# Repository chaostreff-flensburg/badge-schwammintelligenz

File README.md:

# badge-schwammintelligenz

## Ideensammlung
- PCB mit Gehirn-Form und Schwamm-Farbe
  - gelber Lötstopplack
  - nacktes FR4 als Kontrastfarbe für Porösität des Schwammes
  - Konturlinien in schwarzem oder weißem Bestückungsdruck
- viele sehr kleine LEDs auf der Vorderseite
  - blitzen auf, um Neuronen zu mimen
  - mit [Charlieplexing](https://en.wikipedia.org/wiki/Charlieplexing#Origin) kann man 110 LEDs mit nur 11 Pins einzeln ansteuern
    - (`nLedsMax = nGpio * (nGpio - 1)`)
    - [Beispielcode für Charlieplexing](https://goodarduinocode.com/guides/charlieplexing) -> Zeilenweise ansteuern
  - [XINGLIGHT XL0201UWC](https://jlcpcb.com/partdetail/XINGLIGHT-XL0201UWC/C965789) wäre z.B. nur 0,7 mm * 0,4 mm groß (Pads komplett unter dem Package) und kostet nur 0,0326 USD / St. bei 5000 St. Abnahme
- Kompatibilität zu Mesh-Cat-Ears?
  - [Rudelblinken](https://github.com/zebreus/rudelblinken)
  - Die laufen mit BLE auf einem ESP32-C3
  - Wir könnten denselben Controller nutzen, um mit den Katzenohren meshen zu können
- ein Taster auf der Rückseite, um einen Puls auszulösen
  - erstmal an den eigenen LEDs
  - langfristig sonst auch auf Gehirnen in der Nähe
  - evtl. jeder Mesh-Teilnehmer eine eigene LED?
  - 3-4 Taster (Soft touch) (Typ [Alps SKPM](https://tech.alpsalpine.com/e/products/detail/SKPMANE010/)?)

## Implementierung der Farben

Die Platine wird mit **gelbem Lötstopplack** und **weißem Bestückungsdruck** gefertigt.

Kupfer auf der Rückseite minimal halten und wo möglich unter dem Kupfer der Oberseite verlegen.

Der Entwurf sieht folgendermaßen aus:

### Farbaufbau

| Farbe | Objekte | Beteiligte Lagen | Notizen |
| --- | --- | --- | --- |
| weiß | ??? | F.Silkscreen | Bestückungsdruck (muss auf Lötstopplack liegen) |
| silber | ??? | F.Cu, F.Mask | freies Kupfer mit HASL Finish |
| hellergelb | Schwammoberfläche | F.Mask | blankes FR4 (kein Kupfer auf der Rückseite) - ca. `e9d645ff` |
| hellgelb | Vertiefung flach | none | Lötstopplack auf FR4 (kein Kupfer auf der Rückseite) - ca. `f6c50eff` |
| dunkelgelb | Vertiefung tief | F.Cu | Lötstopplack auf Kupfer - ca. `e8b203ff` |
| grüngelb | --- | F.Cu, F.Mask | blankes FR4 mit Kupfer auf der Rückseite |

### Lagenaufbau

| Lage | Objekte |
| --- | --- |
| F.Cu | union( silber, dunkelgelb ) |
| F.Mask | invert( union( weiß, hellgelb, dunkelgelb ) ) |
| F.Silkscreen | weiß |

## BOM

Die folgenden Preise beziehen sich auf ein einzelnes Badge wenn wir Material für 50 Stück kaufen.

- JLCPCB Preis vom 2026-06-15
  - PCB ca. 100 mm x 100 mm
  - Silkscreen gleb
  - 1,6 mm dick
  - LeadFree HASL
  - je 110 St. XINGLIGHT XL-0201UWC (LCSC C965789) von JLCPCB auf der Vorderseite bestückt
  - 258,80 € (Material und Produktion) + 48,03 € (Versand EuroPacket) = 306,83 €
  - Es ist mit 2 Wochen Lieferzeit zu rechnen, wenn es keine Rücksprachen braucht

| Anzahl | Preis | Bezeichnung |
| --- | --- | --- |
| 1 | 6,14 € | PCB mit LEDs (Stand 2026-06-15 von JLCPCB teilbestückt) |
| 1 | ca. 4 € | ESP32-C3 |
| ? | ??? | ??? |

## Firmware

Liegt in `firmware/` und läuft auf dem Waveshare ESP32-C3-Zero.

**Für alle, die einfach ein Badge haben:** Auf https://schwammhirn.c3fl.de/ gibt es alles in
einer Seite. Badge per USB anstecken, „Firmware flashen“ klicken, Port wählen. Danach per
Bluetooth verbinden und steuern. Keine Installation nötig, Chrome oder Edge am Desktop reicht
(zum Steuern auch Chrome auf Android, auf dem iPhone der Browser „Bluefy“).

**Zum Mitentwickeln:** Bauen wahlweise mit der Arduino IDE (Board „Waveshare ESP32-C3-Zero“,
Bibliothek NimBLE-Arduino 2.x) oder mit PlatformIO im Repo-Root: `pio run -t upload`.

- `firmware/led_map.h` wird von `tools/gen_led_map.py` aus `pcb/pcb.kicad_pcb` erzeugt
  (Pin-Paar, Position und Hirnareal jeder LED, die Areale aus den Beschriftungen auf
  Cmts.User). Nach Layoutänderungen neu ausführen, das Skript schreibt auch `web/led_map.js`.
- Ein Timer-Interrupt scannt die Charlieplex-Matrix mit 4 Bit Helligkeit, `loop()`
  rendert Animationen in einen Framebuffer.
- Taster: kurz drücken löst eine Welle aus (auch auf Badges in Reichweite), lang drücken
  wechselt den Modus (Neuronen, Wellen, Cortex, Suche, Laufschrift, Löt-Test). Im Löt-Test startet kurz
  drücken den Durchlauf von vorne. Alle drei Taster liegen auf demselben Eingang.
- Sync: Badges senden Modus, Tempo, Helligkeit, Schriftlayout und Phase per BLE-Advertising.
  Die höchste Änderungsgeneration gewinnt, bei Gleichstand die kleinere ID. Kein
  Verbindungsaufbau nötig. Der Text selbst wird nicht übertragen.
- BLE-Anzeigename ist standardmäßig `Schwammhirn-<ID>` aus der Bluetooth-MAC, änderbar.
  Die Web-Seite findet Badges über die Herstellerkennung im Werbepaket, unabhängig vom Namen.

### Modi

| Modus | Kommando | Was passiert |
| --- | --- | --- |
| Neuronen | `mode neurons` | zufällige Blitze, die ausklingen (Standard) |
| Wellen | `mode pulse` | Ringe laufen von einem zufälligen Punkt nach außen |
| Suche | `mode radar` | Radarstrahl kreist um die Mitte. Je Badge in Reichweite ein Herzschlag-Ring von innen nach außen, schneller und heller je näher (Signalstärke der Werbepakete, −95 dBm weit bis −65 dBm direkt daneben) |
| Cortex | `mode cortex` | ein Hirnareal (Frontal-, Parietal-, Temporal-, Okzipitallappen, Kleinhirn, Stammhirn, aus den Beschriftungen im PCB) blitzt auf, schwächere Wellen laufen von dort in den Rest |
| Laufschrift | `mode text` | Text läuft durch, Größe und Abstand oben einstellbar |
| Löt-Test | `mode test` | füllt jede Zeile LED für LED, dann dunkel, nächste Zeile; danach dasselbe spaltenweise. Jede neue LED wird gemeldet. Fehlt eine LED, ist es die Lötstelle; fehlt eine Zeile oder Spalte, der GPIO oder sein 10-Ω-Widerstand. Wird nicht synchronisiert und nicht gespeichert. |
| Malen | `mode remote` | zeigt ein Rohbild, das per `frame` gesendet wurde (Web-Seite: LEDs antippen) |

### Kommandos (Serial und BLE)

Dieselben Textkommandos gehen über Serial (115200 Baud, USB) und über BLE. BLE nutzt den
Nordic-UART-Service (Schreiben auf `6E400002-…`, Antworten als Notify auf `6E400003-…`),
jede BLE-Terminal-App funktioniert also, zum Beispiel „Serial Bluetooth Terminal“ auf Android.
Eine Zeile pro Kommando, Antwort beginnt mit `ok` oder `err`.

| Kommando | Bedeutung |
| --- | --- |
| `mode <name>` oder `mode <0-6>` | Modus wählen: `neurons`, `pulse`, `cortex`, `radar`, `text`, `test`, `remote` |
| `text <Text>` | Laufschrift setzen, max. 63 Zeichen, Umlaute werden ersetzt, schaltet auf Laufschrift |
| `tsize <1-5>` | Schriftgröße (Leinwand-Pixel pro Font-Pixel), Standard 3 |
| `ty <0-30>` | Abstand der Schrift vom oberen Rand, Standard 6 |
| `speed <0-100>` | Tempo aller Animationen, Standard 4 |
| `bright <1-15>` | Helligkeit, Standard 15 |
| `pulse` oder `pulse <LED 0-109>` | Welle auslösen, auch auf Badges in Reichweite. Im Löt-Test: Durchlauf neu starten |
| `frame <220 Hex-Zeichen>` | Rohbild, ein Byte Helligkeit pro LED in D-Reihenfolge, schaltet auf Malen |
| `name <Name>` | BLE-Anzeigename, max. 20 Zeichen, leer = Standard `Schwammhirn-<ID>` |
| `sync on` / `sync off` | Einstellungen von Badges in der Nähe übernehmen oder ignorieren |
| `mirror on` / `mirror off` | Framebuffer etwa 10-mal pro Sekunde als `F<220 Hex>` per BLE-Notify streamen (Live-Bild der Web-Seite) |
| `peers` | Badges in Reichweite mit ID, Signalstärke, Nähe und Alter des letzten Pakets auflisten |
| `status` | Zustand ausgeben: Modus, Tempo, Helligkeit, Schriftlayout, Text, Sync, Generation, ID, Badges in Reichweite, Name |

Modus, Tempo, Helligkeit, Text, Schriftlayout und Name bleiben über Neustarts erhalten.

### Web-Steuerung

Unter https://schwammhirn.c3fl.de/ oder lokal aus `web/index.html`. „Mit Badge verbinden“
drücken, dann Modi, Text, Regler und Umbenennen. Zeigt live das Bild des Badges, im Modus
„Malen“ lassen sich LEDs antippen. Ohne Verbindung läuft dieselbe Animation als Simulation
1:1 auf der Platinenkontur, so lässt sich zum Beispiel Laufschrift vorab beurteilen.
Web Bluetooth braucht HTTPS oder localhost, deshalb funktioniert Verbinden aus dem
Dateisystem nur in Chrome, das `file://` als sicher behandelt.

Firmware flashen ohne Toolchain: Button „Firmware flashen“ (ESP Web Tools, Chrome/Edge am
Desktop). Die Binaries liegen in `web/flash/`, die Seite zeigt den Commit-Hash der Version.
Nach einer Firmware-Änderung: `pio run`, Code committen, dann `tools/export_firmware.sh` und
die Binaries als eigenen Commit nachschieben.

Deployment: Das `Dockerfile` im Repo-Root liefert `web/` per nginx aus. In Coolify eine
Ressource vom Typ „Public Repository“ mit Build Pack „Dockerfile“ anlegen, Port 80, Domain
eintragen. HTTPS macht Coolify per Let's Encrypt. Nach jedem Merge einmal redeployen.

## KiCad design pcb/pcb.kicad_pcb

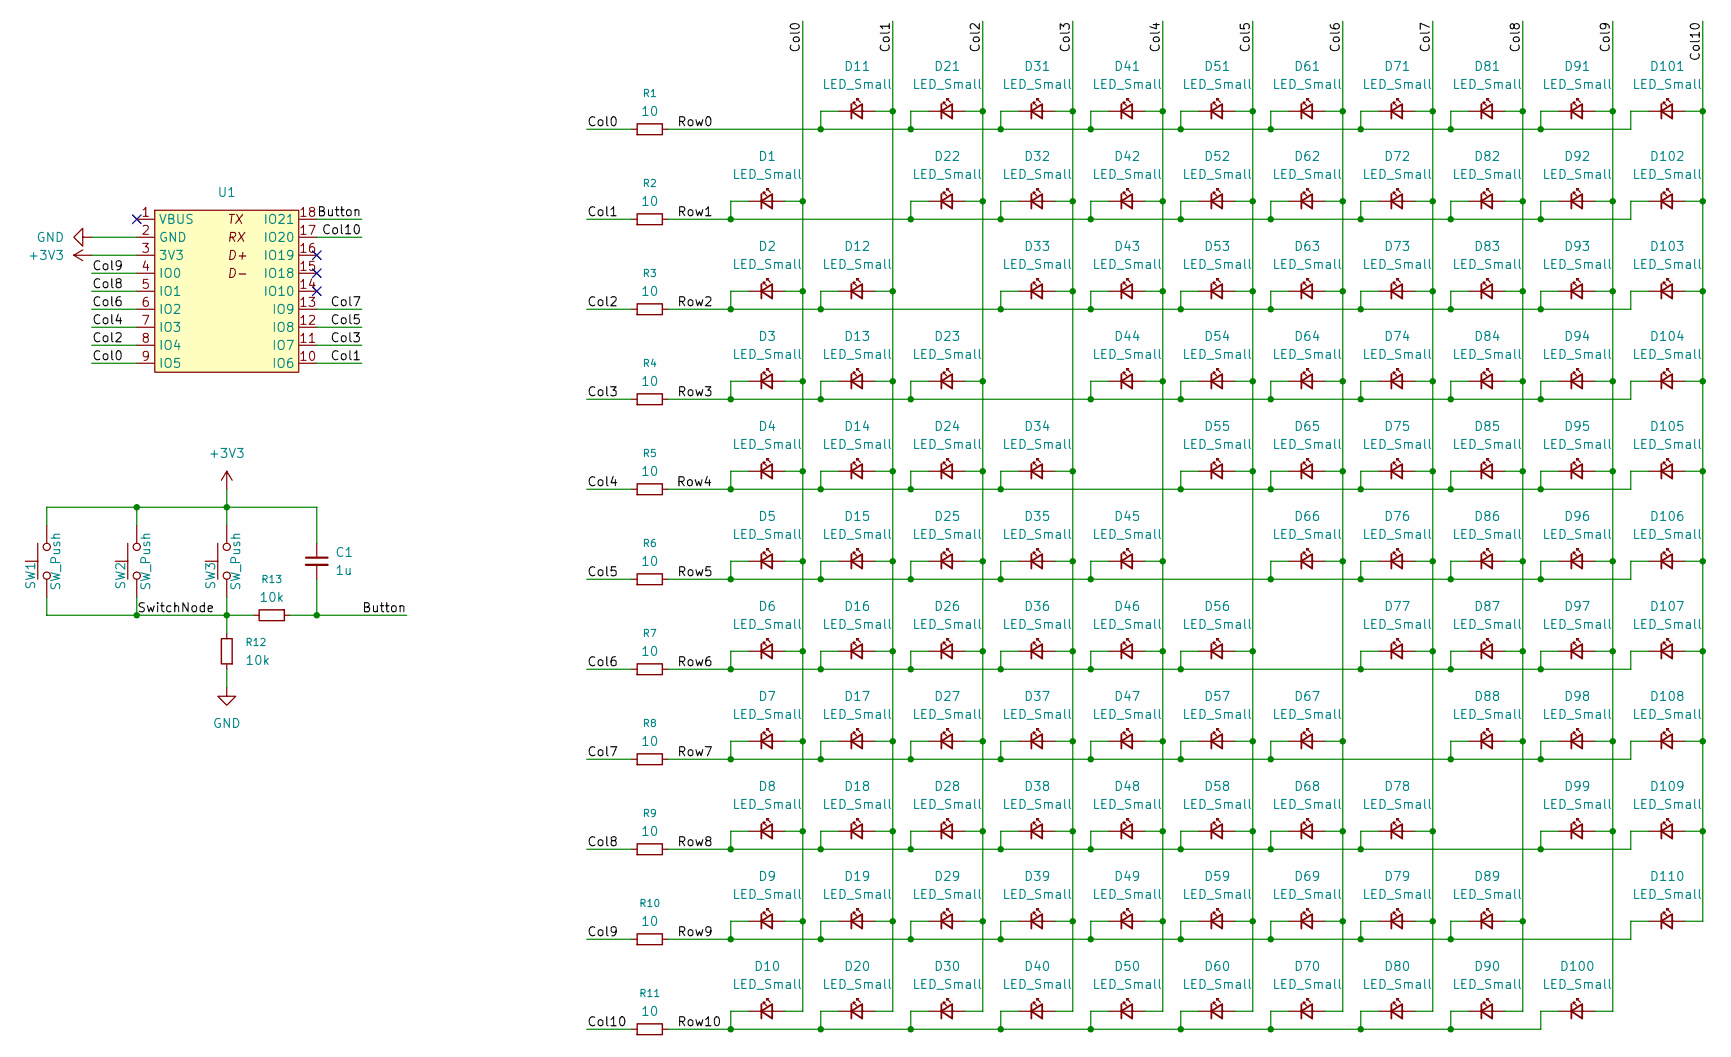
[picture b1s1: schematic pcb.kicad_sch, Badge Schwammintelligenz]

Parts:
C1: 1u; C_0805_2012Metric_Pad1.18x1.45mm_HandSolder
D1, D2, D3, D4, D5, D6, D7, D8, D9, D10, D11, D12, D13, D14, D15, D16, D17, D18, D19, D20, D21, D22, D23, D24, D25, D26, D27, D28, D29, D30, D31, D32, D33, D34, D35, D36, D37, D38, D39, D40, D41, D42, D43, D44, D45, D46, D47, D48, D49, D50, D51, D52, D53, D54, D55, D56, D57, D58, D59, D60, D61, D62, D63, D64, D65, D66, D67, D68, D69, D70, D71, D72, D73, D74, D75, D76, D77, D78, D79, D80, D81, D82, D83, D84, D85, D86, D87, D88, D89, D90, D91, D92, D93, D94, D95, D96, D97, D98, D99, D100, D101, D102, D103, D104, D105, D106, D107, D108, D109, D110: LED_Small; XL-0201; LCSC C965789
R1, R2, R3, R4, R5, R6, R7, R8, R9, R10, R11: 10; R_0805_2012Metric_Pad1.20x1.40mm_HandSolder
R12, R13: 10k; R_0805_2012Metric_Pad1.20x1.40mm_HandSolder
SW1, SW2, SW3: SW_Push; SW_Push_1P1T_NO_Alps_SPEH
U1: Waveshare-ESP32-Cx-Zero

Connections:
+3V3: C1.1, SW1.2, SW2.2, SW3.2, U1.3 (3V3)
/Button: C1.2, R13.1, U1.18 (IO21)
/Col0: D1.2 (A), D2.2 (A), D3.2 (A), D4.2 (A), D5.2 (A), D6.2 (A), D7.2 (A), D8.2 (A), D9.2 (A), D10.2 (A), R1.1, U1.9 (IO5)
/Col1: D11.2 (A), D12.2 (A), D13.2 (A), D14.2 (A), D15.2 (A), D16.2 (A), D17.2 (A), D18.2 (A), D19.2 (A), D20.2 (A), R2.1, U1.10 (IO6)
/Col2: D21.2 (A), D22.2 (A), D23.2 (A), D24.2 (A), D25.2 (A), D26.2 (A), D27.2 (A), D28.2 (A), D29.2 (A), D30.2 (A), R3.1, U1.8 (IO4)
/Col3: D31.2 (A), D32.2 (A), D33.2 (A), D34.2 (A), D35.2 (A), D36.2 (A), D37.2 (A), D38.2 (A), D39.2 (A), D40.2 (A), R4.1, U1.11 (IO7)
/Col4: D41.2 (A), D42.2 (A), D43.2 (A), D44.2 (A), D45.2 (A), D46.2 (A), D47.2 (A), D48.2 (A), D49.2 (A), D50.2 (A), R5.1, U1.7 (IO3)
/Col5: D51.2 (A), D52.2 (A), D53.2 (A), D54.2 (A), D55.2 (A), D56.2 (A), D57.2 (A), D58.2 (A), D59.2 (A), D60.2 (A), R6.1, U1.12 (IO8)
/Col6: D61.2 (A), D62.2 (A), D63.2 (A), D64.2 (A), D65.2 (A), D66.2 (A), D67.2 (A), D68.2 (A), D69.2 (A), D70.2 (A), R7.1, U1.6 (IO2)
/Col7: D71.2 (A), D72.2 (A), D73.2 (A), D74.2 (A), D75.2 (A), D76.2 (A), D77.2 (A), D78.2 (A), D79.2 (A), D80.2 (A), R8.1, U1.13 (IO9)
/Col8: D81.2 (A), D82.2 (A), D83.2 (A), D84.2 (A), D85.2 (A), D86.2 (A), D87.2 (A), D88.2 (A), D89.2 (A), D90.2 (A), R9.1, U1.5 (IO1)
/Col9: D91.2 (A), D92.2 (A), D93.2 (A), D94.2 (A), D95.2 (A), D96.2 (A), D97.2 (A), D98.2 (A), D99.2 (A), D100.2 (A), R10.1, U1.4 (IO0)
/Col10: D101.2 (A), D102.2 (A), D103.2 (A), D104.2 (A), D105.2 (A), D106.2 (A), D107.2 (A), D108.2 (A), D109.2 (A), D110.2 (A), R11.1, U1.17 (IO20)
/Row0: D11.1 (K), D21.1 (K), D31.1 (K), D41.1 (K), D51.1 (K), D61.1 (K), D71.1 (K), D81.1 (K), D91.1 (K), D101.1 (K), R1.2
/Row1: D1.1 (K), D22.1 (K), D32.1 (K), D42.1 (K), D52.1 (K), D62.1 (K), D72.1 (K), D82.1 (K), D92.1 (K), D102.1 (K), R2.2
/Row2: D2.1 (K), D12.1 (K), D33.1 (K), D43.1 (K), D53.1 (K), D63.1 (K), D73.1 (K), D83.1 (K), D93.1 (K), D103.1 (K), R3.2
/Row3: D3.1 (K), D13.1 (K), D23.1 (K), D44.1 (K), D54.1 (K), D64.1 (K), D74.1 (K), D84.1 (K), D94.1 (K), D104.1 (K), R4.2
/Row4: D4.1 (K), D14.1 (K), D24.1 (K), D34.1 (K), D55.1 (K), D65.1 (K), D75.1 (K), D85.1 (K), D95.1 (K), D105.1 (K), R5.2
/Row5: D5.1 (K), D15.1 (K), D25.1 (K), D35.1 (K), D45.1 (K), D66.1 (K), D76.1 (K), D86.1 (K), D96.1 (K), D106.1 (K), R6.2
/Row6: D6.1 (K), D16.1 (K), D26.1 (K), D36.1 (K), D46.1 (K), D56.1 (K), D77.1 (K), D87.1 (K), D97.1 (K), D107.1 (K), R7.2
/Row7: D7.1 (K), D17.1 (K), D27.1 (K), D37.1 (K), D47.1 (K), D57.1 (K), D67.1 (K), D88.1 (K), D98.1 (K), D108.1 (K), R8.2
/Row8: D8.1 (K), D18.1 (K), D28.1 (K), D38.1 (K), D48.1 (K), D58.1 (K), D68.1 (K), D78.1 (K), D99.1 (K), D109.1 (K), R9.2
/Row9: D9.1 (K), D19.1 (K), D29.1 (K), D39.1 (K), D49.1 (K), D59.1 (K), D69.1 (K), D79.1 (K), D89.1 (K), D110.1 (K), R10.2
/Row10: D10.1 (K), D20.1 (K), D30.1 (K), D40.1 (K), D50.1 (K), D60.1 (K), D70.1 (K), D80.1 (K), D90.1 (K), D100.1 (K), R11.2
/SwitchNode: R12.2, R13.2, SW1.1, SW2.1, SW3.1
GND: R12.1, U1.2 (GND)

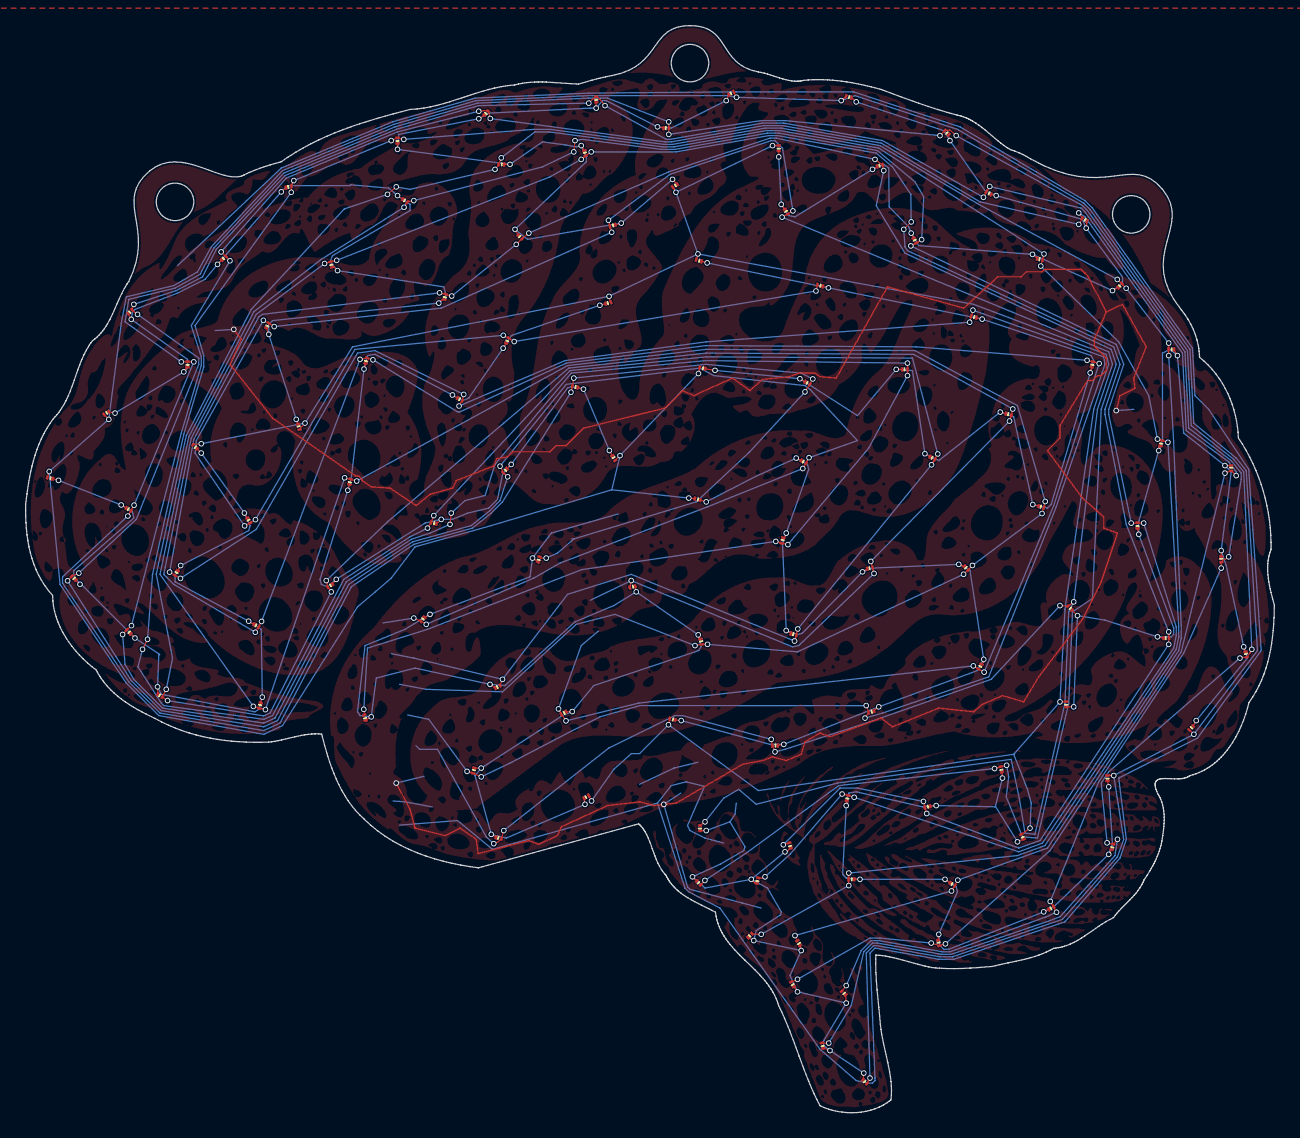
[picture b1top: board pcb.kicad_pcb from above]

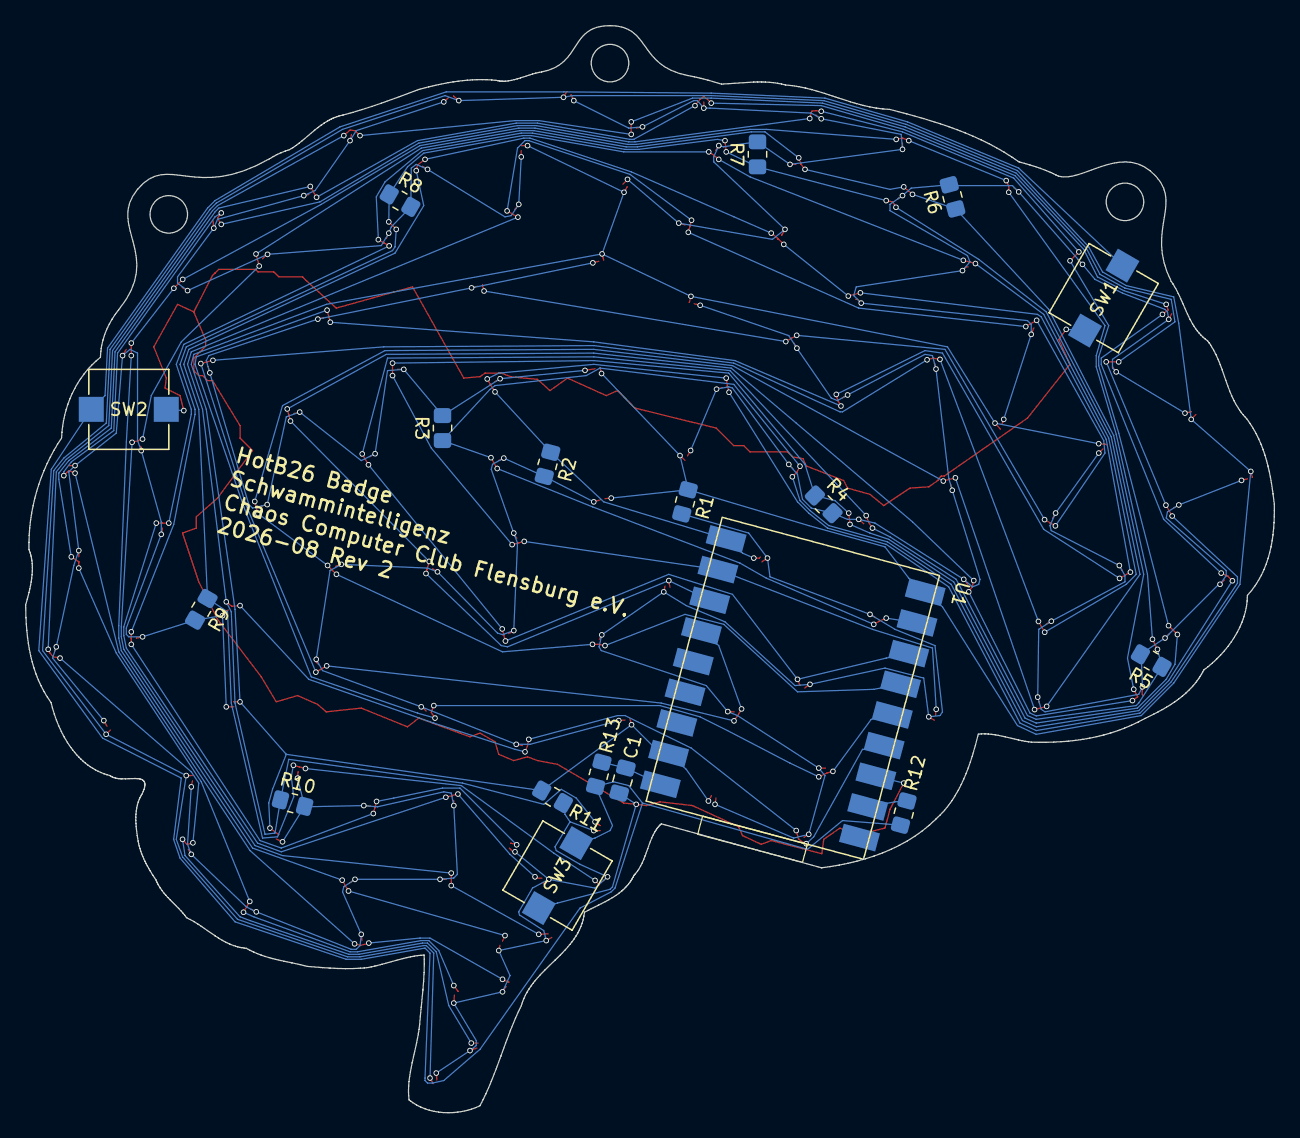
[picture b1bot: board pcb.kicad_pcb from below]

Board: 2 copper layers, 99.9 x 87.0 mm, 128 parts (18 on the bottom side), 26 nets.

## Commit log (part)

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2026-06-03 started taking notes
2026-06-03 moar notes
2026-06-03 notes about specific LEDs and possible meshing with cat ears
2026-06-04 add info about charlieplexing
2026-06-04 ...and made it rendered as code
2026-06-04 add reference to charlieplexing example code
2026-06-14 added placeholder pcb to check for prices circular pcb with 100 mm diameter and 110 XINGLIGHT XL-0201UWC LEDs on the top side but without any connections
2026-06-15 citation added about Rudelblinken
2026-06-23 added new idea for buttons
2026-06-24 Added reference to specific soft touch buttons
